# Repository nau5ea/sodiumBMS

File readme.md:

# Sodium Battery Management System (BMS)

A BMS for sodium-ion 18650 cells in 3S configuration (3 series 18650s)

We used:
* KiCAD for designing schematic/PCB
* STM32 as our microcontroller
* C/C++ for our firmware

This project is GPLv3 licensed

## Authors
* Louis "Buddy" Moench
* Soham Kalbag

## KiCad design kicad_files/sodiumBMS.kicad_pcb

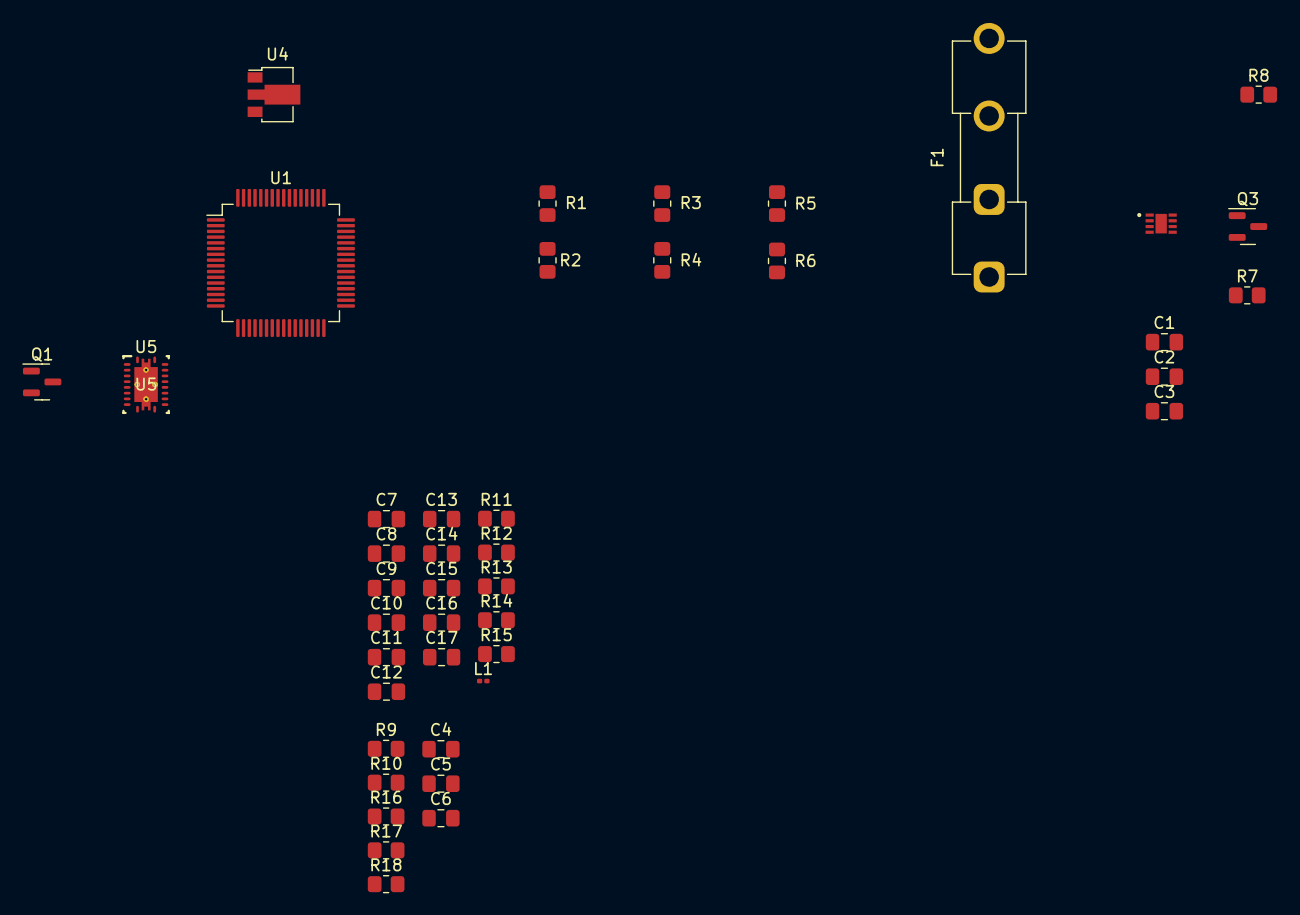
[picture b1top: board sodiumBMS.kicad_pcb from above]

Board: 2 copper layers, 43 parts (0 on the bottom side), 33 nets, no tracks yet.

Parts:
C1, C2, C3: 1.5nF ish; C_0805_2012Metric_Pad1.18x1.45mm_HandSolder
C4: 33uF; C_0805_2012Metric_Pad1.18x1.45mm_HandSolder
C5: 0.47uF; C_0805_2012Metric_Pad1.18x1.45mm_HandSolder
C6: 4.7uF; C_0805_2012Metric_Pad1.18x1.45mm_HandSolder
C7, C9, C17: 10uF; C_0805_2012Metric_Pad1.18x1.45mm_HandSolder
C8: 1uF; C_0805_2012Metric_Pad1.18x1.45mm_HandSolder
C10: 8.2nF; C_0805_2012Metric_Pad1.18x1.45mm_HandSolder
C11: 856.774pF; C_0805_2012Metric_Pad1.18x1.45mm_HandSolder
C12: 40.732pF; C_0805_2012Metric_Pad1.18x1.45mm_HandSolder
C13, C14: 22uF; C_0805_2012Metric_Pad1.18x1.45mm_HandSolder
C15, C16: 100nF; C_0805_2012Metric_Pad1.18x1.45mm_HandSolder
F1: Fuse; Fuseholder_Clip-5x20mm_Eaton_1A5601-01_Inline_P20.80x6.76mm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
L1: 1.4uH; L_0201_0603Metric
Q1, Q3: AO3400A; SOT-23
R1, R4, R6: 20k; R_0805_2012Metric_Pad1.20x1.40mm_HandSolder
R2, R18: 100k; R_0805_2012Metric_Pad1.20x1.40mm_HandSolder
R3: 40k; R_0805_2012Metric_Pad1.20x1.40mm_HandSolder
R5: 60k; R_0805_2012Metric_Pad1.20x1.40mm_HandSolder
R7, R8: 0.05; R_0805_2012Metric_Pad1.20x1.40mm_HandSolder
R9, R10: 5.1k; R_0805_2012Metric_Pad1.20x1.40mm_HandSolder
R11: 162k; R_0805_2012Metric_Pad1.20x1.40mm_HandSolder
R12: 261k; R_0805_2012Metric_Pad1.20x1.40mm_HandSolder
R13: 20.5k; R_0805_2012Metric_Pad1.20x1.40mm_HandSolder
R14: 825k; R_0805_2012Metric_Pad1.20x1.40mm_HandSolder
R15: 92k; R_0805_2012Metric_Pad1.20x1.40mm_HandSolder
R16: 3.3k; R_0805_2012Metric_Pad1.20x1.40mm_HandSolder
R17: 30k; R_0805_2012Metric_Pad1.20x1.40mm_HandSolder
U1: STM32F446RETx; LQFP-64_10x10mm_P0.5mm
U4: LM3940; SOT-89-3
U5: TPS61088RHLR; RHL0020A
U6: INA2180A4; WSON8_DSG_TEX

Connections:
GND: C4.2, C5.2, C6.1, Q3.3 (D), R2.2, R4.2, R6.2, R9.2, R10.2, R18.1, U4.1 (GND), U5.20 (AGND), U5.21 (PGND), U6.4 (GND), U6.9 (GND)
GNDA: C8.2, C10.1, C11.1, C12.1, R12.1, R15.1
unnamed: C1.1, C1.2, R1.1
unnamed: C2.1, C2.2, R3.1
unnamed: C3.1, C3.2, R5.1
unnamed: C11.2, R13.1
unnamed: C16.2, L1.1, R11.2, U5.7 (SW)
unnamed: C7.1, C15.2, L1.2, Q1.3 (D)
unnamed: R16.2, U1.60 (BOOT0)
unnamed: R17.1, R18.2, U1.43 (PA10)
unnamed: C6.2, U1.30 (VCAP_1)
unnamed: C4.1, U1.19 (VDD), U4.3 (VO)
unnamed: C16.1, U5.8 (BOOT)
unnamed: C12.2, R13.2, U5.18 (COMP)
unnamed: R14.2, R15.2, U5.17 (FB)
unnamed: R11.1, U5.3 (FSW)
unnamed: R12.2, U5.19 (ILIM)
unnamed: C10.2, U5.10 (SS)
unnamed: C8.1, U5.1 (VCC)
unnamed: C9.2, C17.2, U5.9 (VIN)
unnamed: R7.2, U6.5 (IN+2)
unnamed: R8.2, U6.2 (IN-1)
PGND: C7.2, C9.1, C13.2, C14.2, C15.1, C17.1
boost_out: C13.1, C14.1, R14.1, U5.14 (VOUT), U5.15 (VOUT), U5.16 (VOUT)
cell1_vsense: R1.2, R2.1, U1.15 (PA1)
cell2_vsense: R3.2, R4.1, U1.16 (PA2)
cell3_vsense: R5.2, R6.1, U1.17 (PA3)
charge_start: Q1.1 (G), U1.27 (PB1)
i_chg_sense: U1.22 (PA6), U6.1 (OUT1)
i_dchg_sense: U1.23 (PA7), U6.7 (OUT2)
mcu_vdd_3.3v: R16.1, U1.32 (VDD)
out_switch: Q3.1 (G), U1.28 (PB2)
usb_5v_in: C5.1, Q1.2 (S), R17.2, U4.2 (VI)

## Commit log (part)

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2026-06-15 switching to nicer control IC for power supply
2026-06-15 finished TI power chip schematic (no values)
2026-06-15 added symbols for TPS and INA2, sim values for TPS
2026-06-15 trying to add ina2180 footprint and symbol but didn't succed on footprint
2026-06-15 got footprint for current sense amp working
2026-06-16 more laying out
2026-06-19 Add USB C programming to schematic, with BOOT/RESET buttons
2026-06-21 Fix sensing schematic and update main schematic
2026-06-21 Add .gitignore
2026-06-21 Remove lck files
2026-06-21 Add discharge current measurement
2026-06-21 i dont rember
2026-06-21 added some gitignore stuff
2026-06-21 Add 3S battery configuration
2026-06-21 Add better comment for battery config
2026-06-24 added spots for constant current and constant voltage charging stages
2026-06-27 Update README with project details and authors
    Expanded project description and added authors section.
2026-06-27 Add charging.kicad_sch
2026-06-27 Remove power supply and add charging schematic instead
2026-06-30 working through what ic to use for PD
